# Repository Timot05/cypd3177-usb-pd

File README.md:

# cypd3177-usb-pd

Wooohooo a new package!

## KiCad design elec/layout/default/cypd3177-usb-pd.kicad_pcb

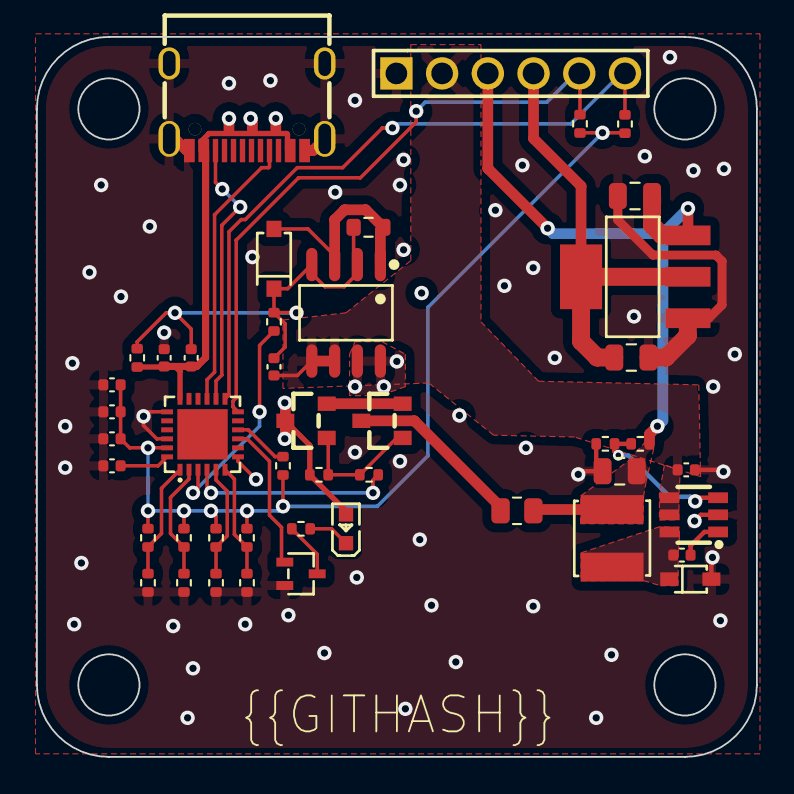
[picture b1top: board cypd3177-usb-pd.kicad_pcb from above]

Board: 2 copper layers, 40.0 x 40.0 mm, 45 parts (0 on the bottom side), 31 nets.

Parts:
C1, C2, C3, C6: 25V 1uF X5R ±10% 0402 Multilayer Ceramic Capacito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; C0402
C4, C5, C10: 16V 100nF X7R ±10% 0402 Multilayer Ceramic Capaci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; C0402
C7: 10V 3.3uF X5R ±10% 0402 Multilayer Ceramic Capaci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; C0402
C8: 6.3V 10uF X5R ±20% 0402 Multilayer Ceramic Capaci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; C0402
C9, C11, C12: 25V 10uF X5R ±10% 0805 Multilayer Ceramic Capacit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; C0805
DS1: SOD-323_L1.8-W1.3-LS2.5-RD
DZ1: SOD-123_L2.7-W1.7-LS3.8-RD
L1: IND-SMD_L4.0-W4.0
LED1: LED0603-RD
R1, R7, R8: 62.5mW Thick Film Resistors 50V ±100ppm/℃ ±1% 10k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; R0402
R2, R5: 62.5mW Thick Film Resistors 50V ±100ppm/℃ ±1% 1kΩ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; R0402
R3: 100mW Thick Film Resistors 75V ±100ppm/℃ ±1% 47kΩ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; R0603
R4: 62.5mW Thick Film Resistors 50V ±100ppm/℃ ±1% 51k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; R0402
R6: 62.5mW Thick Film Resistors 50V ±100ppm/℃ ±1% 4.7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; R0402
R9: 62.5mW Thick Film Resistors ±100ppm/℃ ±0.5% 1.78k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; R0402
R10: 62.5mW Thick Film Resistors ±100ppm/℃ ±1% 316Ω 04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; R0402
R11: 62.5mW Thick Film Resistors 50V ±100ppm/℃ ±1% 54.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; R0402
R12, R14: 62.5mW Thick Film Resistors 50V ±100ppm/℃ ±1% 36.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; R0402
R13, R15: 62.5mW Thick Film Resistors 50V ±100ppm/℃ ±1% 300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; R0402
R16: 62.5mW Thick Film Resistors 50V ±100ppm/℃ ±1% 383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; R0402
R17: 62.5mW Thick Film Resistors 50V ±800ppm/℃ ±1% 0Ω 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; R0402
R18: 62.5mW Thick Film Resistors 50V ±100ppm/℃ ±1% 23.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; R0402
R19: 62.5mW Thick Film Resistors 50V ±100ppm/℃ ±1% 4.3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; R0402
R20: 0 ohm; R0805
U1: USB-C-SMD_KH-TYPE-C-16P
U2: TQFN-24_L4.0-W4.0-P0.50-TL-EP2.8
U3: SOP-8_L4.9-W3.9-P1.27-LS6.0-BL
U4, U5: SOT-23_L2.9-W1.3-P1.90-LS2.4-BR
U6: SOT-323-3_L2.0-W1.3-P1.30-LS2.1-BR
U7: SOT-23-6_L2.9-W1.6-P0.95-LS2.8-BR
U8: SOT-223-3_L6.5-W3.4-P2.30-LS7.0-BR
U9: HDR-TH_6P-P2.54-V-M-1

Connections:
cathode: LED1.1, R9.1
cb: C10.1, U7.1
cc1: U1.A5, U2.15
cc2: U1.B5, U2.14
flip: R6.1, U2.10
gate: R4.2, R5.1, U4.1, U5.1
isnk_coarse: R14.2, R15.1, U2.5
isnk_fine: R16.2, R17.1, U2.6
out: R18.2, R19.1, U7.3
safe_pwr_en: R5.2, U2.4
scl: R8.1, U2.13, U9.6
sda: R7.1, U2.12, U9.5
source: U4.2, U5.2
source1: DZ1.2, R3.1, U3.1, U3.3
sw: C10.2, DS1.1, L1.1, U7.6
usb_c-dm: U1.A7, U1.B7
usb_c-dp: U1.A6, U1.B6
usb_c-gnd: C3.2, C4.2, C5.2, C6.2, C7.2, C8.2, C9.2, C11.2, C12.2, DS1.2, R11.2, R13.2, R15.2, R17.2, R19.2, U1.1, U1.2, U1.3, U1.4, U1.A1, U1.A12, U1.B1, U1.B12, U2.19, U2.22, U6.2, U7.2, U8.1, U9.1
usb_c-vcc: C1.1, C7.1, LED1.2, R1.1, R4.1, U1.A4, U1.A9, U1.B4, U1.B9, U2.18, U3.7, U3.8, U4.3
usb_pd_device-vcc: R20.1, U5.3
usb_pd_device.cypd3177_ic-vcc: U2.9, U6.1
usb_pd_device.cypd3177_ic-vcc-1: C3.1, C4.1, C5.1, R6.2, R7.2, R8.2, R10.1, R12.1, R14.1, R16.1, U2.23
usb_pd_device.cypd3177_ic-vcc-2: C6.1, U2.24
usb_pd_device.led_indicator.led-gnd: R9.2, U6.3
usb_pd_device.load_switch.load_switch_mosfet-gnd: C1.2, C2.2, DZ1.1, R1.2, R2.1, R3.2, U3.2, U3.4
vbus_fet_en: R2.2, U2.3
vbus_max: R12.2, R13.1, U2.2
vbus_min: R10.2, R11.1, U2.1
vcc: C2.1, C8.1, U3.5, U3.6, U7.4, U7.5, U9.2
vcc-1: C9.1, C11.1, L1.2, R18.1, R20.2, U8.3, U9.3
vcc-2: C12.1, U8.2, U8.4, U9.4

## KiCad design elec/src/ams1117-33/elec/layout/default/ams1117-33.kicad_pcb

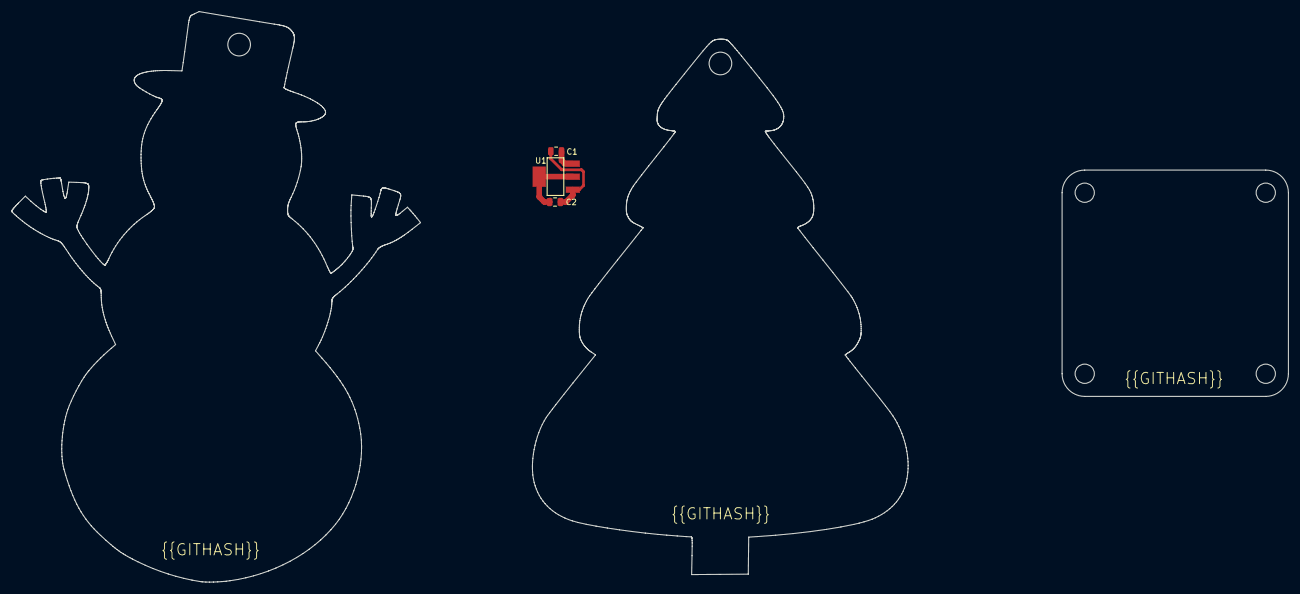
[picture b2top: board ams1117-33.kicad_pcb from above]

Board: 2 copper layers, 66.4 x 94.6 mm, 3 parts (0 on the bottom side), 3 nets.

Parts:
C1, C2: 25V 10uF X5R ±10% 0805 Multilayer Ceramic Capacit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; C0805
U1: SOT-223-3_L6.5-W3.4-P2.30-LS7.0-BR

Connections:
gnd: C1.2, C2.2, U1.1
vcc: C1.1, U1.3
vcc-1: C2.1, U1.2, U1.4

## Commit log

2024-04-18 Configure project
2024-04-18 add vdivs, regs and load switch
2024-04-19 layout progress
2024-04-19 add complete layout
2024-04-19 fix CI build
2024-04-19 fix for production
2024-04-19 add fields
2024-04-20 fix connection
